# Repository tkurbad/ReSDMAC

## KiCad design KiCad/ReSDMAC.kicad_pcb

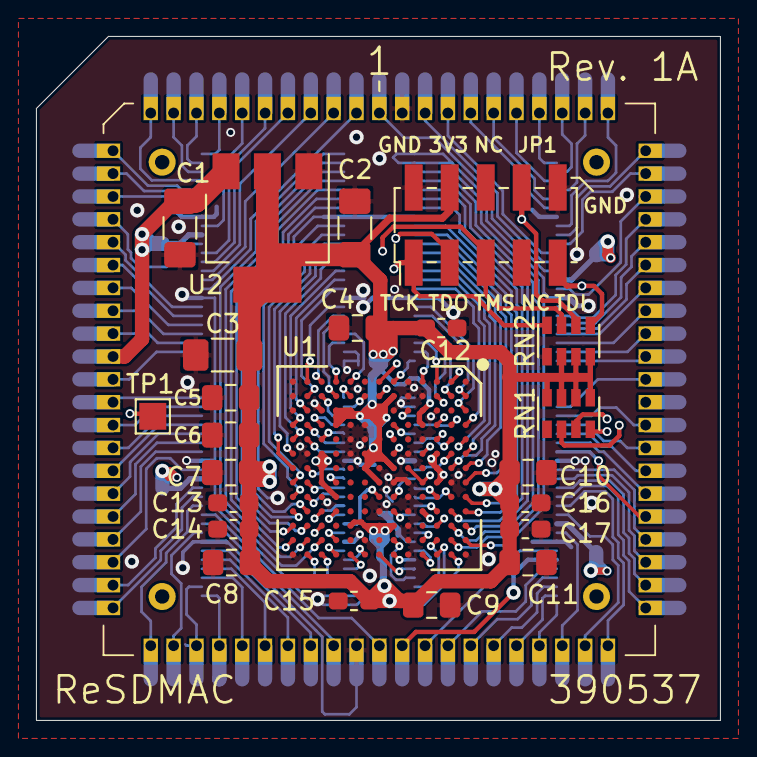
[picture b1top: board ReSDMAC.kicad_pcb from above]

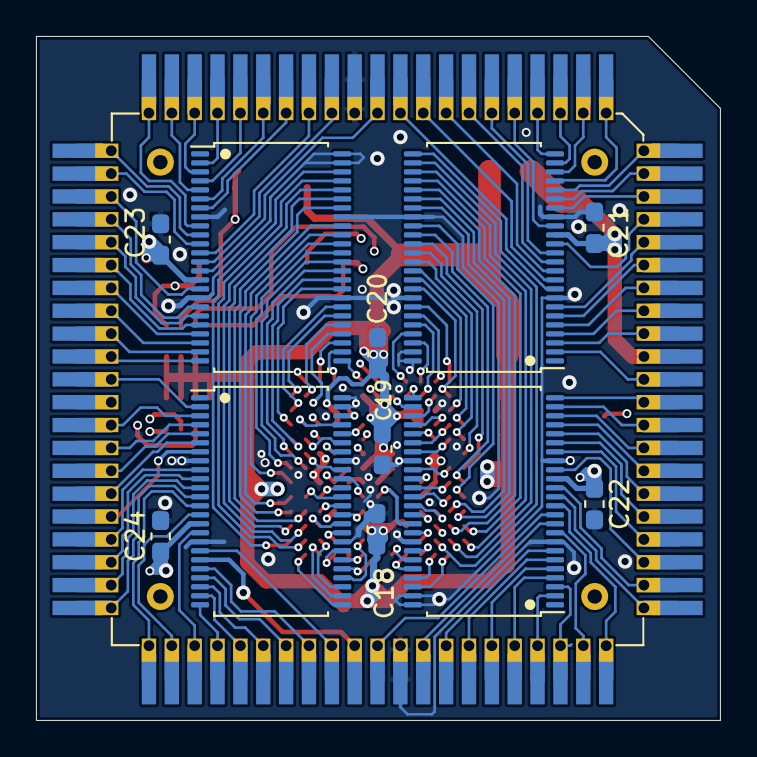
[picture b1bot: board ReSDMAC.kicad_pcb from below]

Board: 4 copper layers, 38.0 x 38.0 mm, 36 parts (12 on the bottom side), 172 nets.

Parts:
C1, C2, C3: 10uF; C_1206_3216Metric_Pad1.42x1.75mm_HandSolder
C4, C5, C8, C11: 1uF; C_0805_2012Metric_Pad1.15x1.40mm_HandSolder
C6, C7, C9, C10: 0.1uF; C_0805_2012Metric_Pad1.15x1.40mm_HandSolder
C12, C13, C14, C15, C16, C17, C18, C19, C21, C22, C23, C24: 0.01uF; C_0603_1608Metric_Pad1.05x0.95mm_HandSolder
C20: 0.1uF; C_0603_1608Metric_Pad1.05x0.95mm_HandSolder
JTAG1: Conn_02x05_Odd_Even; PinHeader_2x05_P2.00mm_Vertical_SMD
RN1, RN2: 10k; RESCAF80P320X160X60-8N
TP1: TestPoint_Small; TestPoint_Pad_1.5x1.5mm
U1: 10M02SCU169C8G; BGA-169_11.0x11.0mm_Layout13x13_P0.8mm_Ball0.5mm_Pad0.35mm_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
U2: LM1117-3.3; SOT-223
U3, U4, U5, U6: SN74CBTD16210; TSSOP-48_6.1x12.5mm_P0.5mm_padLength_1mm
U7: PLCC_84_plug; PLCC-84_Plug_P1.27mm_mirrored
U8: Super_DMAC_socket; PLCC-84_TH_pin_holes

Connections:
3V3: C2.2, C3.2, C4.2, C5.2, C6.2, C7.2, C8.2, C9.2, C10.2, C11.2, C12.2, C13.2, C14.2, C15.2, C16.2, C17.2, C18.2, C19.2, C20.2, JTAG1.4, RN1.5, RN1.6, RN1.7, RN1.8, RN2.6, RN2.7, RN2.8, U1.C6, U1.C7, U1.C8, U1.D3, U1.D4, U1.D10, U1.F2, U1.F7, U1.F11, U1.G3, U1.G4, U1.G5, U1.G6, U1.G8, U1.G11, U1.H3, U1.H6, U1.H7, U1.H11, U1.J3, U1.J11, U1.K3, U1.K4, U1.K9, U1.L6, U1.L7, U1.L8, U2.2, U2.4
A2: U3.5, U7.76, U8.76
A2_FPGA: U1.A11, U3.43
A3: U3.3, U7.77, U8.77
A3_FPGA: U1.B12, U3.45
A4: U3.2, U7.78, U8.78
A4_FPGA: U1.A12, U3.46
A5: U3.4, U7.79, U8.79
A5_FPGA: U1.B11, U3.44
A6: U3.6, U7.80, U8.80
A6_FPGA: U1.B10, U3.42
AS: U6.5, U7.38, U8.38
AS_FPGA: U1.H13, U6.43
BERR: U5.21, U7.47, U8.47
BERR_FPGA: U1.F12, U5.28
BGACK: U3.13, U7.83, U8.83
BGACK_FPGA: U1.A6, U3.35
CONF_DONE: RN1.3, U1.C5
CPUCLK: U5.19, U7.44, U8.44
CPUCLK_FPGA: U1.F13, U5.30
CSS: U3.22, U7.67, U8.67
CSS_FPGA: U1.C1, U3.27
CSX0: U3.19, U7.70, U8.70
CSX0_FPGA: U1.A2, U3.30
CSX1: U3.18, U7.71, U8.71
CSX1_FPGA: U1.A3, U3.31
D0: U3.14, U7.1, U8.1
D0_FPGA: U1.A5, U3.34
D1: U4.9, U7.2, U8.2
D1_FPGA: U1.M3, U4.39
D2: U4.10, U7.3, U8.3
D2_FPGA: U1.N4, U4.38
D3: U4.11, U7.4, U8.4
D3_FPGA: U1.N5, U4.37
D4: U4.12, U7.5, U8.5
D4_FPGA: U1.N6, U4.36
D5: U4.13, U7.6, U8.6
D5_FPGA: U1.N7, U4.35
D6: U4.16, U7.7, U8.7
D6_FPGA: U1.N9, U4.33
D7: U4.24, U7.8, U8.8
D7_FPGA: U1.L12, U4.25
D8: U4.23, U7.9, U8.9
D8_FPGA: U1.M12, U4.26
D9: U4.22, U7.10, U8.10
D9_FPGA: U1.N12, U4.27
D10: U4.21, U7.11, U8.11
D10_FPGA: U1.N11, U4.28
D11: U4.20, U7.12, U8.12
D11_FPGA: U1.M11, U4.29
D12: U4.19, U7.13, U8.13
D12_FPGA: U1.N10, U4.30
D13: U4.18, U7.14, U8.14
D13_FPGA: U1.M10, U4.31
D14: U4.14, U7.15, U8.15
D14_FPGA: U1.N8, U4.34
D15: U4.7, U7.16, U8.16
D15_FPGA: U1.M2, U4.40
D16: U4.6, U7.17, U8.17
D16_FPGA: U1.M1, U4.42
D17: U4.5, U7.18, U8.18
D17_FPGA: U1.L1, U4.43
D18: U4.4, U7.19, U8.19
D18_FPGA: U1.K2, U4.44
D19: U4.3, U7.20, U8.20
D19_FPGA: U1.J1, U4.45
D20: U4.2, U7.22, U8.22
D20_FPGA: U1.K1, U4.46
D21: U6.24, U7.23, U8.23
D21_FPGA: U1.J2, U6.25
D22: U6.23, U7.24, U8.24
D22_FPGA: U1.H2, U6.26
D23: U6.22, U7.25, U8.25
D23_FPGA: U1.L2, U6.27
D24: U6.21, U7.26, U8.26
D24_FPGA: U1.L4, U6.28
D25: U6.20, U7.27, U8.27
D25_FPGA: U1.L5, U6.29
D26: U6.19, U7.28, U8.28
D26_FPGA: U1.M4, U6.30
D27: U6.18, U7.29, U8.29
D27_FPGA: U1.M5, U6.31
D28: U6.16, U7.30, U8.30
D28_FPGA: U1.M7, U6.33
D29: U6.14, U7.31, U8.31
D29_FPGA: U1.K8, U6.34
D30: U6.13, U7.32, U8.32
D30_FPGA: U1.M8, U6.35
D31: U6.12, U7.33, U8.33
D31_FPGA: U1.M9, U6.36
DACK: U3.23, U7.66, U8.66
DACK_FPGA: U1.D1, U3.26
DMAEN: U3.9, U7.75, U8.75
DMAEN_FPGA: U1.A9, U3.39
DREQ: U3.24, U7.65, U8.65
DREQ_FPGA: U1.F1, U3.25
DS: U6.6, U7.39, U8.39
DSACK0: U6.10, U7.41, U8.41
DSACK0_FPGA: U1.K10, U6.38
DSACK1: U6.7, U7.40, U8.40
DSACK1_FPGA: U1.K12, U6.40
DS_FPGA: U1.K13, U6.42
GND: C1.1, C2.1, C3.1, C4.1, C5.1, C6.1, C7.1, C8.1, C9.1, C10.1, C11.1, C12.1, C13.1, C14.1, C15.1, C16.1, C17.1, C18.1, C19.1, C20.1, C21.1, C22.1, C23.1, C24.1, JTAG1.2, JTAG1.10, RN2.5, U1.A1, U1.A13, U1.B8, U1.C3, U1.D2, U1.D5, U1.D7, U1.E1, U1.E2, U1.E6, U1.E8, U1.E9, U1.E10, U1.E11, U1.E12, U1.E13, U1.F3, U1.F8, U1.G7, U1.G10, U1.H4, U1.H5, U1.H12, U1.J4, U1.J5, U1.J6, U1.L3, U1.L9, U1.M6, U1.N1, U1.N2, U1.N3, U1.N13, U2.1, U3.8, U3.17, U3.32, U3.41, U3.47, U3.48, U4.8, U4.17, U4.32, U4.41, U4.47, U4.48, U5.8, U5.17, U5.32, U5.41, U5.47, U5.48, U6.8, U6.17, U6.32, U6.41, U6.47, U6.48, U7.42, U7.84, U8.42, U8.84
INC_ADD: U3.10, U7.74, U8.74
INC_ADD_FPGA: U1.A8, U3.38
INT2: U6.3, U7.35, U8.35
INT2_FPGA: U1.L13, U6.45
INTA: U3.11, U7.73, U8.73
INTA_FPGA: U1.A7, U3.37
INTB: U6.9, U7.34, U8.34
INTB_FPGA: U1.G9, U6.39
IOR: U3.20, U7.69, U8.69
IORDY: U3.16, U7.72, U8.72
IORDY_FPGA: U1.A4, U3.33
IORST: U5.20, U7.46, U8.46
IORST_FPGA: U1.G13, U5.29
IOR_FPGA: U1.B2, U3.29
IOW: U3.21, U7.68, U8.68
IOW_FPGA: U1.C2, U3.28
JP1: JTAG1.8, RN2.2, U1.B1
PD0: U5.22, U7.48, U8.48
PD0_FPGA: U1.C12, U5.27
PD1: U5.23, U7.49, U8.49
PD1_FPGA: U1.C13, U5.26
PD2: U5.24, U7.50, U8.50
PD2_FPGA: U1.B13, U5.25
PD3: U5.16, U7.51, U8.51
PD3_FPGA: U1.D12, U5.33
PD4: U5.14, U7.52, U8.52
PD4_FPGA: U1.C11, U5.34
PD5: U5.13, U7.53, U8.53
PD5_FPGA: U1.F10, U5.35
PD6: U5.12, U7.54, U8.54
PD6_FPGA: U1.C10, U5.36
PD7: U5.11, U7.55, U8.55
PD7_FPGA: U1.B9, U5.37
PD8: U5.10, U7.56, U8.56
PD8_FPGA: U1.C9, U5.38
PD9: U5.9, U7.57, U8.57
PD9_FPGA: U1.F9, U5.39
PD10: U5.7, U7.58, U8.58
PD10_FPGA: U1.B6, U5.40
PD11: U5.6, U7.59, U8.59
PD11_FPGA: U1.D6, U5.42
PD12: U5.5, U7.60, U8.60
PD12_FPGA: U1.B5, U5.43
PD13: U5.4, U7.61, U8.61
PD13_FPGA: U1.F4, U5.44
PD14: U5.3, U7.62, U8.62
PD14_FPGA: U1.B4, U5.45
PD15: U5.2, U7.64, U8.64
PD15_FPGA: U1.E3, U5.46
RW: U6.4, U7.37, U8.37
RW_FPGA: U1.J13, U6.44
SBG: U3.12, U7.82, U8.82
SBG_FPGA: U1.B7, U3.36
SBR: U3.7, U7.81, U8.81
SBR_FPGA: U1.A10, U3.40
SCSI: U5.18, U7.45, U8.45
SCSI_FPGA: U1.D13, U5.31
SIZ1: U6.2, U7.36, U8.36
SIZ1_FPGA: U1.M13, U6.46
STERM: U6.11, U7.43, U8.43
STERM_FPGA: U1.L10, U6.37
TCK: JTAG1.1, RN2.4, U1.G2
TDI: JTAG1.9, RN2.1, U1.F5
TDO: JTAG1.3, U1.F6
TMS: JTAG1.5, RN2.3, U1.G1
TP1: TP1.1, U1.L11
VCC: C1.2, C21.2, C22.2, C23.2, C24.2, U2.3, U3.15, U4.15, U5.15, U6.15, U7.21, U7.63, U8.21, U8.63
nCONFIG: RN1.4, U1.D8, U1.E7
nSTATUS: RN1.2, U1.C4

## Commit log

2025-03-20 Production files
2025-04-08 Added JLC production files w/ 10M04 Added pof for 0.9
2025-04-08 Added 10M04 pof for 0.9
